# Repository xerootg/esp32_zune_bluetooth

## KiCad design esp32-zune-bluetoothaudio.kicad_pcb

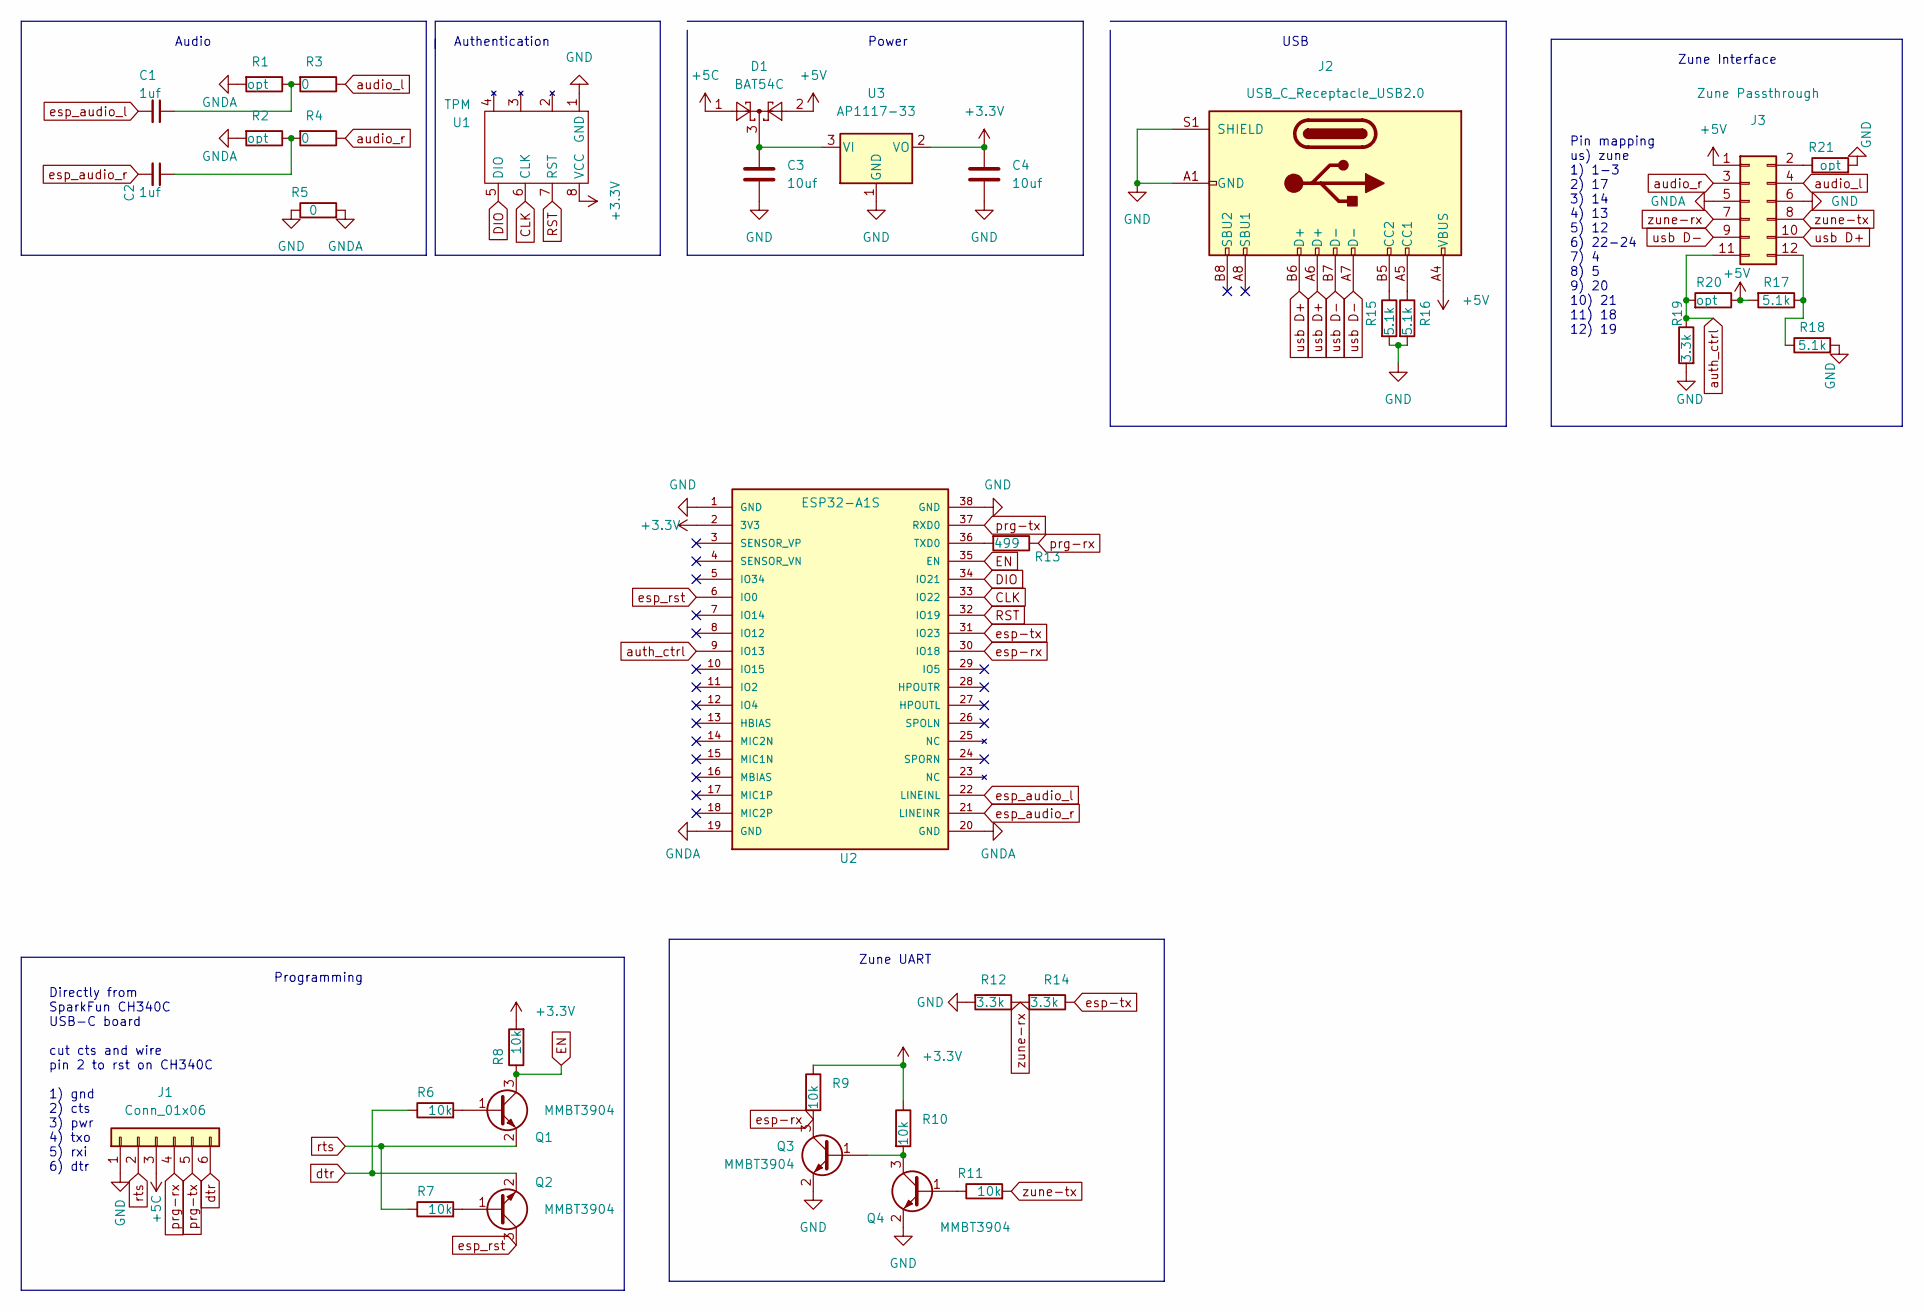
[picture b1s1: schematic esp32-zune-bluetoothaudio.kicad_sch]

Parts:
C1, C2: 1uf; C_0805_2012Metric_Pad1.18x1.45mm_HandSolder
C3, C4: 10uf; C_0805_2012Metric_Pad1.18x1.45mm_HandSolder
D1: BAT54C; SOT-23
J1: Conn_01x06; PinHeader_1x06_P2.54mm_Vertical
J2: USB_C_Receptacle_USB2.0; USB_C_Receptacle_XKB_U262-16XN-4BVC11
J3: Zune Passthrough; PinHeader_2x06_P2.00mm_Vertical_SMD
Q1, Q2, Q3, Q4: MMBT3904; SOT-23
R1, R2, R20, R21: opt; R_0805_2012Metric_Pad1.20x1.40mm_HandSolder
R3, R4, R5: 0; R_0805_2012Metric_Pad1.20x1.40mm_HandSolder
R6, R7, R8, R9, R10, R11: 10k; R_0805_2012Metric_Pad1.20x1.40mm_HandSolder
R12, R14, R19: 3.3k; R_0805_2012Metric_Pad1.20x1.40mm_HandSolder
R13: 499; R_0805_2012Metric_Pad1.20x1.40mm_HandSolder
R15, R16, R17, R18: 5.1k; R_0805_2012Metric_Pad1.20x1.40mm_HandSolder
U1: TPM; Infineon_PG-DSO-8-27_3.9x4.9mm_EP2.65x3mm
U2: ESP32-A1S; PARTREV 4
U3: AP1117-33; SOT-223-3_TabPin2

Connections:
+3.3V: C4.1, R8.2, R9.1, R10.1, U1.8 (VCC), U2.2 (3V3), U3.2 (VO)
+5C: D1.1, J1.3
+5V: D1.2, J2.A4 (VBUS), J2.A9 (VBUS), J2.B4 (VBUS), J2.B9 (VBUS), J3.1, R17.2, R20.1
CLK: U1.6 (CLK), U2.33 (IO22)
DIO: U1.5 (DIO), U2.34 (IO21)
EN: Q1.3 (C), R8.1, U2.35 (EN)
GND: C3.2, C4.2, J1.1, J2.A1 (GND), J2.A12 (GND), J2.B1 (GND), J2.B12 (GND), J2.S1 (SHIELD), J3.6, Q3.2 (E), Q4.2 (E), R5.1, R12.2, R15.2, R16.2, R18.2, R19.2, R21.2, U1.1 (GND), U2.1 (GND), U2.38 (GND), U3.1 (GND)
GNDA: J3.5, R1.2, R2.2, R5.2, U2.19 (GND), U2.20 (GND)
unnamed: C1.1, R1.1, R3.2
unnamed: C2.1, R2.1, R4.2
unnamed: C3.1, D1.3, U3.3 (VI)
unnamed: J2.A5 (CC1), R16.1
unnamed: J2.B5 (CC2), R15.1
unnamed: Q1.1 (B), R6.2
unnamed: Q2.1 (B), R7.2
unnamed: Q3.1 (B), Q4.3 (C), R10.2
unnamed: Q4.1 (B), R11.1
unnamed: R13.2, U2.36 (TXD0)
unnamed: J3.12, R17.1, R18.1
unnamed: J3.2, R21.1
RST: U1.7 (RST), U2.32 (IO19)
audio_l: J3.4, R3.1
audio_r: J3.3, R4.1
auth_ctrl: J3.11, R19.1, R20.2, U2.9 (IO13)
dtr: J1.6, Q2.2 (E), R6.1
esp-rx: Q3.3 (C), R9.2, U2.30 (IO18)
esp-tx: R14.1, U2.31 (IO23)
esp_audio_l: C1.2, U2.22 (LINEINL)
esp_audio_r: C2.2, U2.21 (LINEINR)
esp_rst: Q2.3 (C), U2.6 (IO0)
prg-rx: J1.4, R13.1
prg-tx: J1.5, U2.37 (RXD0)
rts: J1.2, Q1.2 (E), R7.1
usb D+: J2.A6 (D+), J2.B6 (D+), J3.10
usb D-: J2.A7 (D-), J2.B7 (D-), J3.9
zune-rx: J3.7, R12.1, R14.2
zune-tx: J3.8, R11.2

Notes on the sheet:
Zune Interface
Pin mapping us) zune 1) 1-3 2) 17 3) 14 4) 13 5) 12 6) 22-24 7) 4 8) 5 9) 20 10) 21 11) 18 12) 19
Zune UART
Authentication
USB
Audio
Programming
Power
Directly from SparkFun CH340C USB-C board cut cts and wire pin 2 to rst on CH340C 1) gnd 2) cts 3) pwr 4) txo 5) rxi 6) dtr

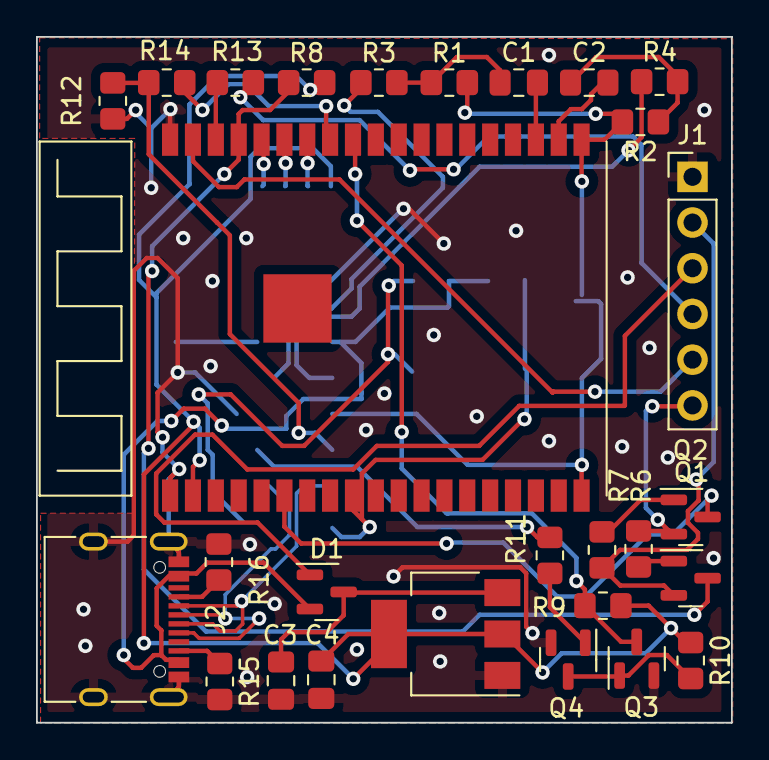
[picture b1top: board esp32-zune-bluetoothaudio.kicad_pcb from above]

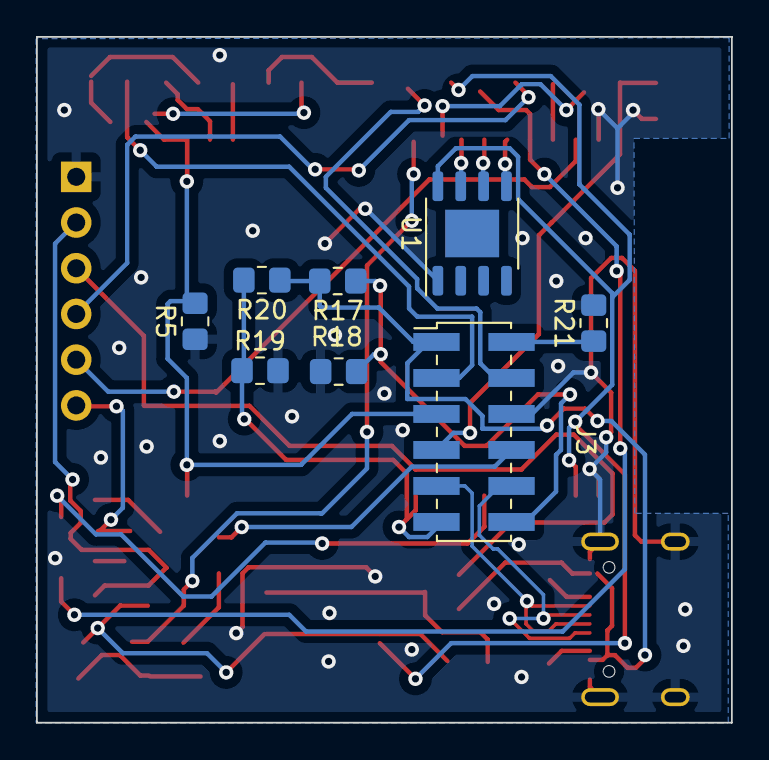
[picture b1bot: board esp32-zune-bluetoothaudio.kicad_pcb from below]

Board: 2 copper layers, 38.6 x 38.1 mm, 36 parts (8 on the bottom side), 37 nets.

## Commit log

2023-01-10 Got a start atleast
2023-01-10 just for you internet
2023-01-21 remove the backups
2023-01-21 cleanup a bit, add level shifting
2023-01-23 Needs gain adjustment, uart commands, uart actually hooked up... but we have audio. on a dev board anyway.
2023-01-23 update to represent the state of the breadboard
2023-01-25 send data to the xbox chip
2023-01-25 starting to write a zune "driver", updating schematic to match breadboard. I'm getting close to laying out a pcb.
2023-01-27 Symbols mostly associated, almost ready for PCB
2023-01-27 well... its a pcb without routing and its too big. gonna try to make it a two board layout, placing the esp32 behind the body of the zune.
2023-01-27 layoutish
2023-01-27 well, this is what I submitted for fabrication validation
2023-01-29 we can receive packets from the zune now!
2023-01-30 forward auth requests to the xbox chip plz
2023-01-31 Currently, the xbox chip is not working. I am working on that, but in the meantime, here's significant cleanup.
2023-01-31 make the xbox driver return length
2023-01-31 this seems to abort before it's supposed to. im gonna backport the "old" driver to the new header, but this is here for if i need it.
